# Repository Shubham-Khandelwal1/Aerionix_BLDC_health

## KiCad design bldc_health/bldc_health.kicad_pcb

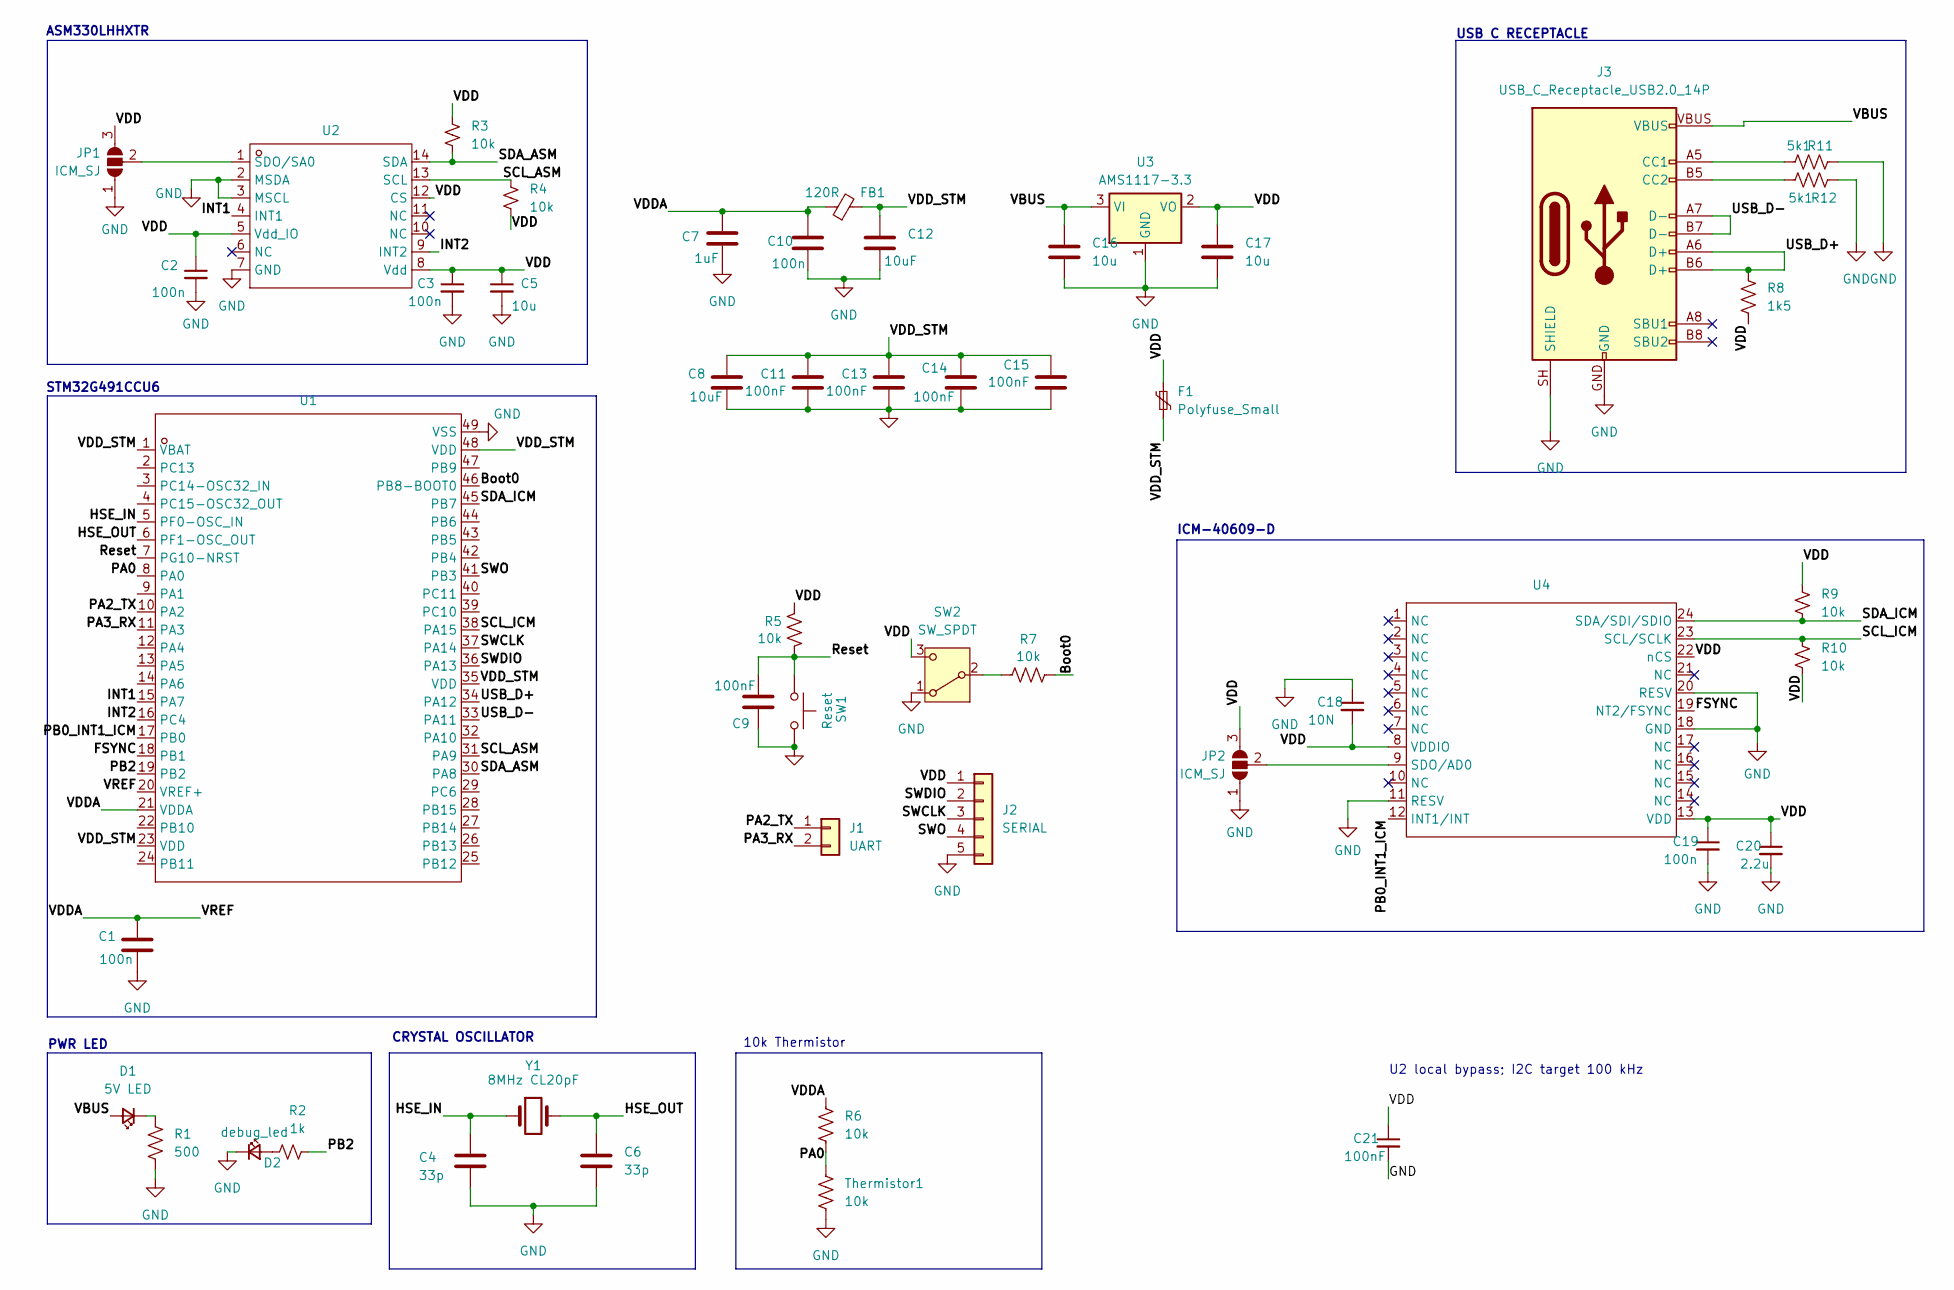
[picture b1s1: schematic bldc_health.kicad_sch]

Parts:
C1, C2, C3, C10, C19: 100n; C_0603_1608Metric_Pad1.08x0.95mm_HandSolder
C4, C6: 33p; C_0603_1608Metric_Pad1.08x0.95mm_HandSolder
C5, C16, C17: 10u; C_0603_1608Metric_Pad1.08x0.95mm_HandSolder
C7: 1uF; C_0603_1608Metric_Pad1.08x0.95mm_HandSolder
C8, C12: 10uF; C_0603_1608Metric_Pad1.08x0.95mm_HandSolder
C9, C11, C13, C14, C15: 100nF; C_0603_1608Metric_Pad1.08x0.95mm_HandSolder
C18: 10N; C_0603_1608Metric_Pad1.08x0.95mm_HandSolder
C20: 2.2u; C_0603_1608Metric_Pad1.08x0.95mm_HandSolder
C21: 100nF; C_0402_1005Metric
D1: 5V LED; LED_0805_2012Metric_Pad1.15x1.40mm_HandSolder
D2: debug_led; LED_0805_2012Metric_Pad1.15x1.40mm_HandSolder
F1: Polyfuse_Small; Fuse_0603_1608Metric_Pad1.05x0.95mm_HandSolder
FB1: 120R; L_0603_1608Metric_Pad1.05x0.95mm_HandSolder
J1: UART; PinHeader_1x02_P2.54mm_Vertical
J2: SERIAL; PinHeader_1x05_P2.54mm_Vertical
J3: USB_C_Receptacle_USB2.0_14P; USB-C-16P_ARM-PCB
JP1, JP2: ICM_SJ; SolderJumper-3_P1.3mm_Open_Pad1.0x1.5mm
R1: 500; R_0603_1608Metric_Pad0.98x0.95mm_HandSolder
R2: 1k; R_0603_1608Metric_Pad0.98x0.95mm_HandSolder
R3, R4, R5, R6, R7, R9, R10: 10k; R_0603_1608Metric_Pad0.98x0.95mm_HandSolder
R8: 1k5; R_0603_1608Metric_Pad0.98x0.95mm_HandSolder
R11, R12: 5k1; R_0603_1608Metric_Pad0.98x0.95mm_HandSolder
SW1: Reset; SW_TS09-63-25-WT-160-SMT-TR
SW2: SW_SPDT; SW_Slide-03_Wuerth-WS-SLTV_10x2.5x6.4_P2.54mm
Thermistor1: 10k; PinHeader_1x02_P1.00mm_Vertical
U1: UFQFPN-48_L7.0-W7.0-P0.50-TL-EP5.6; Manufacturer Part STM32G491CCU6; LCSC Part Name 主流的 Arm Cortex-M4 微控制器，主频 170 MHz，配备 25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
U2: LGA-14_L3.0-W2.5-P0.50-TL; Manufacturer Part ASM330LHHXTR; LCSC Part Name 高精度6轴汽车惯性测量单元
U3: AMS1117-3.3; SOT-223-3_TabPin2
U4: ICM-40609-D_LGA24_DirectGround; Manufacturer Part ICM-40609-D; LCSC Part Name 6轴MEMS运动跟踪设备
Y1: 8MHz CL20pF; Crystal_SMD_HC49-SD

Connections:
/Boot0: R7.2, U1.46 (PB8-BOOT0)
/FSYNC: U1.18 (PB1), U4.19 (NT2/FSYNC)
/HSE_IN: C4.1, U1.5 (PF0-OSC_IN), Y1.1
/HSE_OUT: C6.1, U1.6 (PF1-OSC_OUT), Y1.2
/INT1: U1.15 (PA7), U2.4 (INT1)
/INT2: U1.16 (PC4), U2.9 (INT2)
/PA0: R6.2, Thermistor1.1, U1.8 (PA0)
/PA2_TX: J1.1, U1.10 (PA2)
/PA3_RX: J1.2, U1.11 (PA3)
/PB0_INT1_ICM: U1.17 (PB0), U4.12 (INT1/INT)
/PB2: R2.2, U1.19 (PB2)
/Reset: C9.2, R5.1, SW1.1, U1.7 (PG10-NRST)
/SCL_ASM: R4.1, U1.31 (PA9), U2.13 (SCL)
/SCL_ICM: R10.1, U1.38 (PA15), U4.23 (SCL/SCLK)
/SDA_ASM: R3.2, U1.30 (PA8), U2.14 (SDA)
/SDA_ICM: R9.2, U1.45 (PB7), U4.24 (SDA/SDI/SDIO)
/SWCLK: J2.3, U1.37 (PA14)
/SWDIO: J2.2, U1.36 (PA13)
/SWO: J2.4, U1.41 (PB3)
/USB_D+: J3.A6 (D+), J3.B6 (D+), R8.1, U1.34 (PA12)
/USB_D-: J3.A7 (D-), J3.B7 (D-), U1.33 (PA11)
/VBUS: C16.1, D1.2 (A), J3.VBUS, U3.3 (VI)
/VDD: C2.1, C3.1, C5.1, C17.1, C18.2, C19.1, C20.1, C21.1, F1.1, J2.1, JP1.3 (B), JP2.3 (B), R3.1, R4.2, R5.2, R8.2, R9.1, R10.2, SW2.3 (C), U2.5 (Vdd_IO), U2.8 (Vdd), U2.12 (CS), U3.2 (VO), U4.8 (VDDIO), U4.13 (VDD), U4.22 (nCS)
/VDDA: C1.1, C7.1, C10.1, FB1.1, R6.1, U1.20 (VREF+), U1.21 (VDDA)
/VDD_STM: C8.1, C11.1, C12.1, C13.1, C14.1, C15.1, F1.2, FB1.2, U1.1 (VBAT), U1.23 (VDD), U1.35 (VDD), U1.48 (VDD)
GND: C1.2, C2.2, C3.2, C4.2, C5.2, C6.2, C7.2, C8.2, C9.1, C10.2, C11.2, C12.2, C13.2, C14.2, C15.2, C16.2, C17.2, C18.1, C19.2, C20.2, C21.2, D2.1 (K), J2.5, J3.GND, J3.SH (SHIELD), JP1.1 (A), JP2.1 (A), R1.2, R11.2, R12.2, SW1.2, SW2.1 (A), Thermistor1.2, U1.49 (VSS), U2.2 (MSDA), U2.3 (MSCL), U2.7 (GND), U3.1 (GND), U4.11 (RESV), U4.18 (GND), U4.20 (RESV); also elsewhere on the board
unnamed: D1.1 (K), R1.1
unnamed: D2.2 (A), R2.1
unnamed: J3.A5 (CC1), R11.1
unnamed: J3.B5 (CC2), R12.1
unnamed: JP1.2 (C), U2.1 (SDO/SA0)
unnamed: JP2.2 (C), U4.9 (SDO/AD0)
unnamed: R7.1, SW2.2 (B)

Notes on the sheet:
STM32G491CCU6
USB C RECEPTACLE
ICM-40609-D
ASM330LHHXTR
10k Thermistor
PWR LED
CRYSTAL OSCILLATOR
U2 local bypass; I2C target 100 kHz

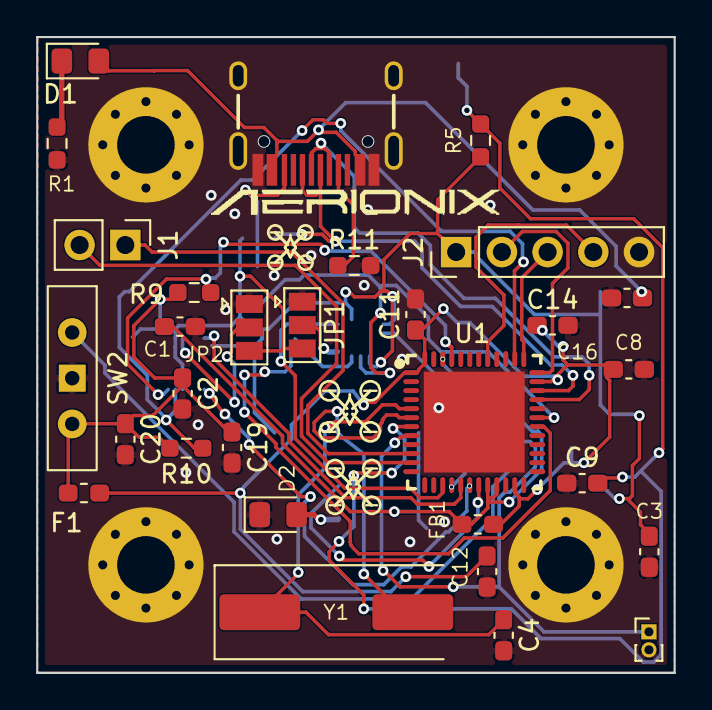
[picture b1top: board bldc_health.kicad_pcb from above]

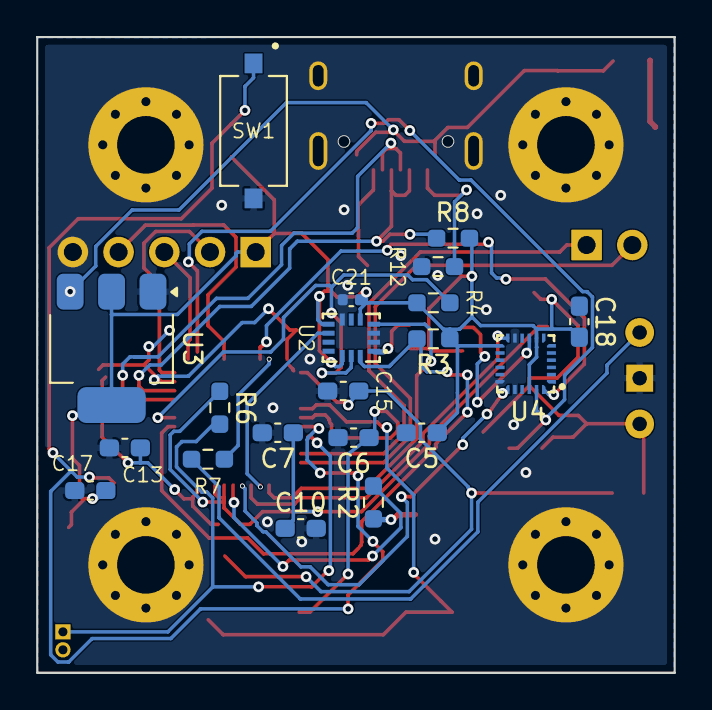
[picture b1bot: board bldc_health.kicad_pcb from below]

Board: 2 copper layers, 35.4 x 35.3 mm, 54 parts (24 on the bottom side), 33 nets.

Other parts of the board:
MH2, MH5, MH6, MH7: MountingHole_M3; MountingHole_3.2mm_M3_Pad_Via

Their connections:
GND: MH2.1, MH5.1, MH6.1, MH7.1; also elsewhere on the board
